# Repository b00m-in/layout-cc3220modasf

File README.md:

## [Contents](#contents)

Original CC3220MODASF footprint downloaded from Ultralibrarian.

see ~/dev/kicad/cc3220s/wifi_module/ul_CC3220MODASF12MONR/ (pls ignore - this is a local path) for original CC3220MODASF footprint. Some border lines and through holes in the middle thermal ground pads had to be removed and replaced with vias on the board. 

P.Cu is in fact a ground plane and G.Cu is a power plane

The order of the interface jumpers has changed between CC3220S-LAUNCHXL and LAUNCH-CC3220MODASF. On the former VCC_BRD and VBATT_CC could be jumped as they were next to one another. 

Also J9 came jumped on the former so U7 (op-amp in adc circuit) was powered by VCC_BRD but it's not jumped by default on the latter - didn't catch that as the adc functionality hasn't been yet tested on the latter.  

TMP006AIYZFR is obsolete so was replaced by TMP116NAIDRVR 

## [Layout](#layout)

The following GPIO ports were left unconnected due to space constraints on board:
```
P05_GPIO_14
P06_GPIO_15
P07_GPIO_16
P08_GPIO_17
P18_GPIO_28
P45_GPIO_31 / DCDC_ANA2_SW_P - not connected on dev board either
DCDC_ANA2_SW_N (P46) 
```

CC3220S/F <-> CC3220MODAS
```
Pin55 GPIO1 UART0_TX <-> Pin46
Pin57 GPIO2 UART0_RX <-> Pin47

Pin07 GPIO16 UART1_TX <-> Pin07
Pin08 GPIO17 UART1_RX <-> Pin08
```
~/ti/ccsv8/simplelink_cc32xx_sdk_3_10_00_04/source/ti/boards/CC3220S_LAUNCHXL/CC3220S_LAUNCHXL.c
.rxPin = UARTCC32XX_PIN_08_UART1_RX --> .rxPin = UARTCC32XX_PIN_45_UART1_RX

### [References](#references)
+ 
+  
+

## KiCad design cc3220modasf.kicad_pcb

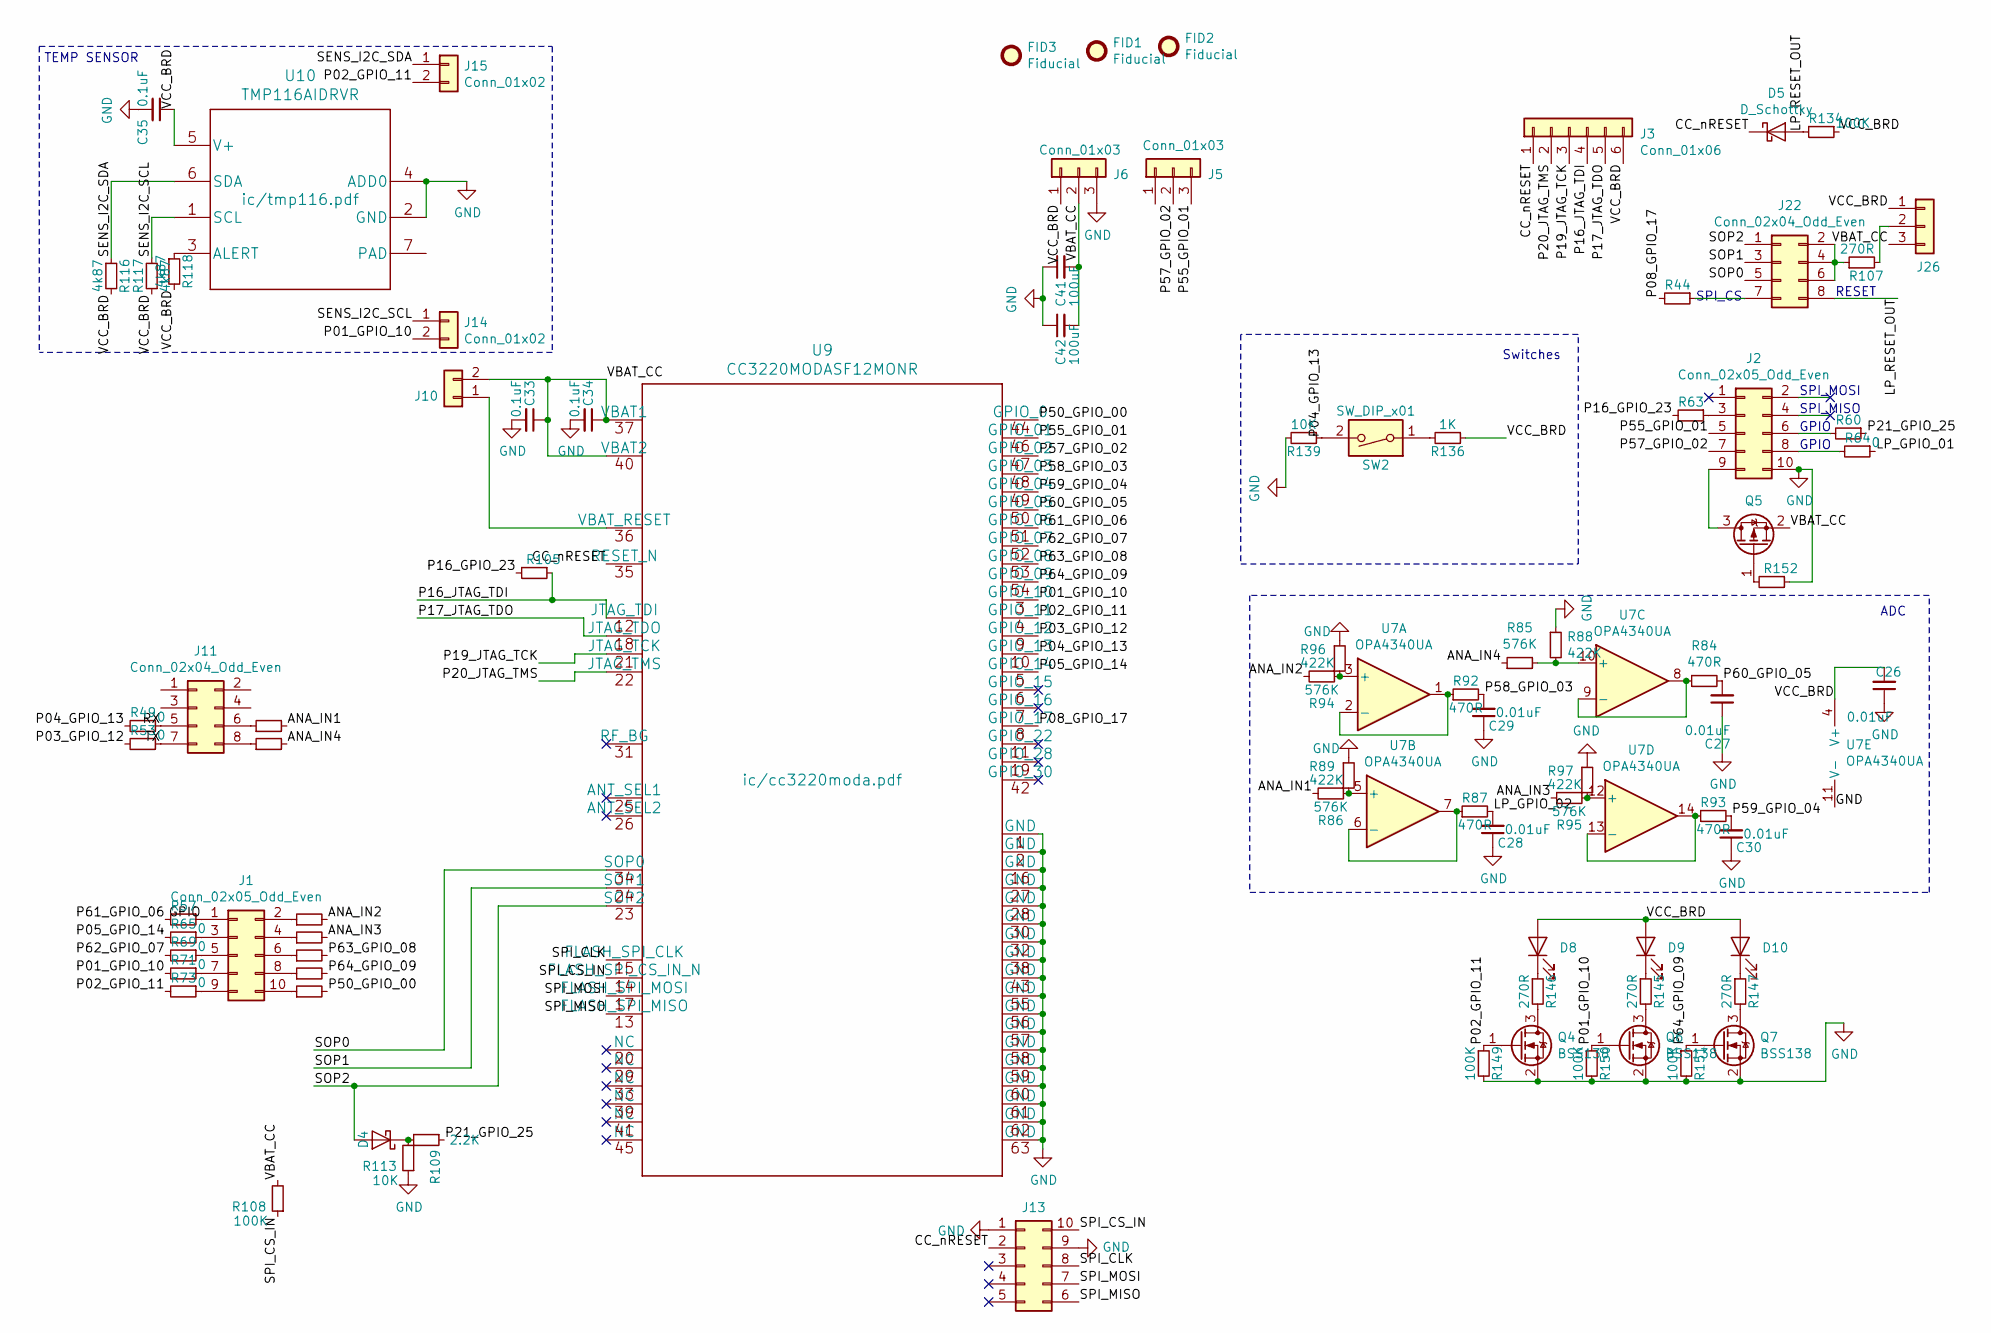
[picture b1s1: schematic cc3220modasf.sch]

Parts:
C26: 0.01uF; C_0402_1005Metric; MFG Part Num GRM155R61A103KA01D
C27, C28, C29, C30: 0.01uF; C_0402_1005Metric; MFG Part Num C1005X7R1C103K
C33, C34, C35: 0.1uF; C_0402_1005Metric; MFG Part Num GRM155R61A104KA01D
C41, C42: 100uF; C_1206_3216Metric; MFG Part Num GRM31CR60J107ME39L
D4, D5: D_Schottky; D_0603_1608Metric; MFG Part Num CD0603-B0240R/B00340
D8: GREEN LED; LED_0603_1608Metric; MFG Part Num SML-LX0603GW-TR
D9: YELLOW LED; LED_0603_1608Metric; MFG Part Num 150060YS75000
D10: RED LED; LED_0603_1608Metric; MFG Part Num SML-311UTT86
FID1, FID2, FID3: Fiducial; Fiducial_0.5mm_Mask1mm
J1, J2: Conn_02x05_Odd_Even; PinHeader_2x05_P2.54mm_Vertical; MFG Part Num TSW-105-15-G-D
J3: Conn_01x06; PinSocket_1x06_P2.54mm_Vertical; MFG Part Num '61301021121
J5, J6: Conn_01x03; PinSocket_1x03_P2.54mm_Vertical
J10, J14, J15: Conn_01x02; PinHeader_1x02_P2.54mm_Vertical; MFG Part Num '61300211121
J11, J22: Conn_02x04_Odd_Even; PinHeader_2x04_P2.54mm_Vertical
J13: Conn_02x05_Counter_Clockwise; Tag-Connect_TC2050-IDC-NL_2x05_P1.27mm_Vertical_CC_SMD
J26: Conn_01x03; PinHeader_1x03_P2.54mm_Vertical; MFG Part Num '61300311121
Q4, Q6, Q7: BSS138; SOT-23; MFG Part Num BSS138
Q5: FDN358P; SuperSOT-3; MFG Part Num FDN358P
R44, R49, R50, R53, R54, R57, R58, R60, R62, R63, R64, R65, R66, R69, R71, R72, R73, R74, R105, R152: 0; R_0402_1005Metric; MFG Part Num ERJ-2GE0R00X
R84, R87, R92, R93: 470R; R_0402_1005Metric; MFG Part Num ERJ-2RKF4700X
R85, R86, R94, R95: 576K; R_0402_1005Metric; MFG Part Num CRCW0402576KFKED
R88, R89, R96, R97: 422K; R_0402_1005Metric; MFG Part Num CRCW0402422KFKED
R107: 270R; R_0603_1608Metric; MFG Part Num CRCW0603270RJNEA
R108: 100K; R_0402_1005Metric; MFG Part Num CRCW0402100KDHEDP
R109: 2.2K; R_0402_1005Metric; MFG Part Num CRCW04022K20JNED
R113: 10K; R_0402_1005Metric; MFG Part Num CRCW040210K0JNED
R116, R117, R118: 4k87; R_0603_1608Metric; MFG Part Num CRCW06034K87FKEA
R134: 100K; R_0402_1005Metric; MFG Part Num CRCW0402100KJNED
R136: 1K; R_0402_1005Metric; MFG Part Num CRCW04021K00JNEDC
R139: 10K; R_0402_1005Metric; MFG Part Num CRCW040210K0JNEDC
R145, R146, R147: 270R; R_0603_1608Metric; MFG Part Num CRCW0603270RJNEAC
R149, R150, R151: 100K; R_0402_1005Metric; MFG Part Num CRCW0402100KJNEDC
SW2: SW_DIP_x01; SW_Tactile_SPST_Angled_PTS645Vx31-2LFS; MFG Part Num MJTP1117
U7: OPA4340UA; TSSOP-14_4.4x5mm_P0.65mm; MFG Part Num OPA4342EA/250
U9: CC3220MODASF12MONR; MFG Part Num CC3220MODASF12MON
U10: TMP116AIDRVR; MFG Part Num TMP116NAIDRVR

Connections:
/ANA_IN1: R50.2, R86.2
/ANA_IN2: R58.2, R94.2
/ANA_IN3: R62.2, R95.2
/ANA_IN4: R54.2, R85.1
/CC_nRESET: D5.1 (K), J3.1, J13.2, U9.35 (RESET_N)
/GPIO: J1.1, R57.1
/LP_GPIO_02: C28.2, R87.2
/LP_RESET_OUT: D5.2 (A), J22.8, R134.2
/P01_GPIO_10: J14.2, Q6.1 (G), R71.2, R150.1, U9.3 (GPIO_10)
/P02_GPIO_11: J15.2, Q4.1 (G), R73.2, R149.1, U9.4 (GPIO_11)
/P03_GPIO_12: R53.2, U9.9 (GPIO_12)
/P04_GPIO_13: R49.2, R139.1, SW2.2, U9.10 (GPIO_13)
/P05_GPIO_14: R65.2, U9.5 (GPIO_14)
/P08_GPIO_17: R44.2, U9.8 (GPIO_17)
/P16_GPIO_23: R63.2, R105.2
/P16_JTAG_TDI: J3.4, R105.1, U9.12 (JTAG_TDI)
/P17_JTAG_TDO: J3.5, U9.18 (JTAG_TDO)
/P19_JTAG_TCK: J3.3, U9.21 (JTAG_TCK)
/P20_JTAG_TMS: J3.2, U9.22 (JTAG_TMS)
/P21_GPIO_25: R60.1, R109.1
/P50_GPIO_00: R74.2, U9.44 (GPIO_0)
/P55_GPIO_01: J2.5, J5.3, U9.46 (GPIO_01)
/P57_GPIO_02: J2.7, J5.2, U9.47 (GPIO_02)
/P58_GPIO_03: C29.2, R92.2, U9.48 (GPIO_03)
/P59_GPIO_04: C30.2, R93.2, U9.49 (GPIO_04)
/P60_GPIO_05: C27.2, R84.2, U9.50 (GPIO_05)
/P61_GPIO_06: R57.2, U9.51 (GPIO_06)
/P62_GPIO_07: R69.2, U9.52 (GPIO_07)
/P63_GPIO_08: R66.2, U9.53 (GPIO_08)
/P64_GPIO_09: Q7.1 (G), R72.2, R151.1, U9.54 (GPIO_09)
/RX: J11.5, R49.1
/SENS_I2C_SCL: J14.1, R117.2, U10.1 (SCL)
/SENS_I2C_SDA: J15.1, R116.1, U10.6 (SDA)
/SOP0: J22.5, U9.34 (SOP0)
/SOP1: J22.3, U9.24 (SOP1)
/SOP2: D4.2 (A), J22.1, U9.23 (SOP2)
/SPI_CLK: J13.8, U9.15 (FLASH_SPI_CLK)
/SPI_CS_IN: J13.10, R108.1, U9.14 (FLASH_SPI_CS_IN_N)
/SPI_MISO: J13.6, U9.13 (FLASH_SPI_MISO)
/SPI_MOSI: J13.7, U9.17 (FLASH_SPI_MOSI)
/TX: J11.7, R53.1
/VBAT_CC: C33.1, C34.1, C41.2, C42.2, J6.2, J10.2, J26.3, Q5.2 (S), R108.2, U9.37 (VBAT1), U9.40 (VBAT2)
/VCC_BRD: C26.2, C35.1, D8.2 (A), D9.2 (A), D10.2 (A), J3.6, J6.1, J26.1, R116.2, R117.1, R118.2, R134.1, R136.1, U7.4 (V+), U10.5 (V+)
GND: C26.1, C27.1, C28.1, C29.1, C30.1, C33.2, C34.2, C35.2, C41.1, C42.1, J2.10, J6.3, J13.1, J13.9, Q4.2 (S), Q6.2 (S), Q7.2 (S), R88.1, R89.1, R96.1, R97.1, R113.1, R139.2, R149.2, R150.2, R151.2, R152.1, U7.11 (V-), U9.1 (GND), U9.2 (GND), U9.16 (GND), U9.27 (GND), U9.28 (GND), U9.30 (GND), U9.32 (GND), U9.38 (GND), U9.43 (GND), U9.55 (GND), U9.56 (GND), U9.57 (GND), U9.58 (GND), U9.59 (GND), U9.60 (GND), U9.61 (GND), U9.62 (GND), U9.63 (GND), U10.2 (GND), U10.4 (ADD0)
unnamed: D4.1 (K), R109.2, R113.2
unnamed: D8.1 (K), R146.1
unnamed: D9.1 (K), R145.1
unnamed: D10.1 (K), R147.1
unnamed: J1.2, R58.1
unnamed: J1.3, R65.1
unnamed: J1.4, R62.1
unnamed: J1.5, R69.1
unnamed: J1.6, R66.1
unnamed: J1.7, R71.1
unnamed: J1.8, R72.1
unnamed: J1.9, R73.1
unnamed: J1.10, R74.1
unnamed: J2.3, R63.1
unnamed: J2.6, R60.2
unnamed: J2.8, R64.2
unnamed: J2.9, Q5.3 (D)
unnamed: J10.1, U9.36 (VBAT_RESET)
unnamed: J11.6, R50.1
unnamed: J11.8, R54.1
unnamed: J22.2, J22.4, J22.6, R107.1
unnamed: J22.7, R44.1
unnamed: J26.2, R107.2
unnamed: Q4.3 (D), R146.2
unnamed: Q5.1 (G), R152.2
unnamed: Q6.3 (D), R145.2
unnamed: Q7.3 (D), R147.2
unnamed: R84.1, U7.8, U7.9 (-)
unnamed: R85.2, R88.2, U7.10 (+)
unnamed: R86.1, R89.2, U7.5 (+)
unnamed: R87.1, U7.6 (-), U7.7
unnamed: R92.1, U7.1, U7.2 (-)
unnamed: R93.1, U7.13 (-), U7.14
unnamed: R94.1, R96.2, U7.3 (+)
unnamed: R95.1, R97.2, U7.12 (+)
unnamed: R118.1, U10.3 (ALERT)
unnamed: R136.2, SW2.1

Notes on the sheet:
Switches
TEMP SENSOR
ADC
GPIO
SPI_MISO
SPI_MOSI
RESET
SPI_CS

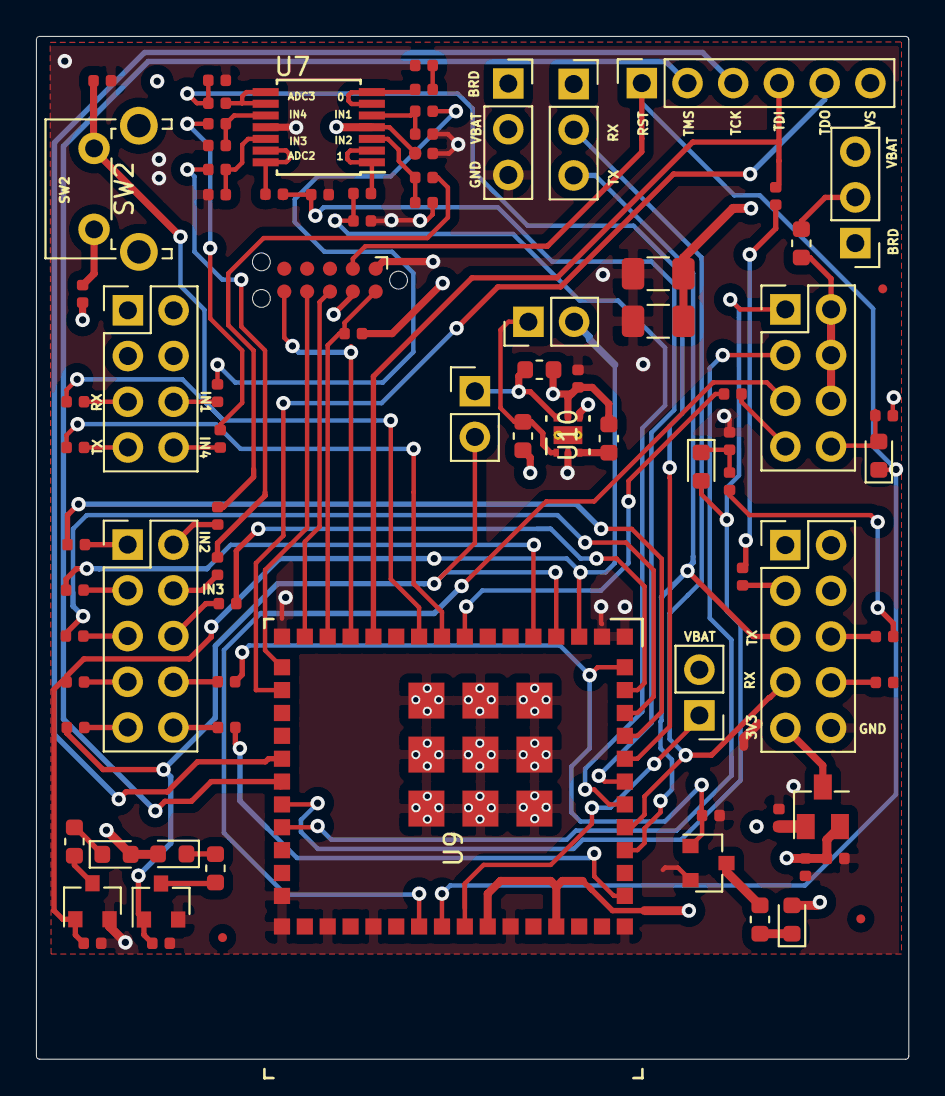
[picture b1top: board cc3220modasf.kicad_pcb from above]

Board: 4 copper layers, 48.5 x 56.8 mm, 86 parts (0 on the bottom side), 81 nets.

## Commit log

2020-11-27 Changed U10 to TMP116AIDRVR. Added new sybmol/footprint bom, pos files and README into repo.
2021-05-10 Updated readme, added screenshot

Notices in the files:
parts and their libraries:
Copyright 2016 Accelerated Designs. All rights reserved.
